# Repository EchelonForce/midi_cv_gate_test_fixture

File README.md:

# MIDI to 16x16 CV Gate Module Test Fixture

This the KiCAD design of a test fixture for the MIDI to 16x16 CV Gate Module

Full writeup here: https://www.robotdialogs.com/2023/03/test-fixture-and-calibration-eurorack.html

This work is licensed under a Creative Commons Attribution-NonCommercial-ShareAlike 4.0 International License. https://creativecommons.org/licenses/by-nc-sa/4.0/

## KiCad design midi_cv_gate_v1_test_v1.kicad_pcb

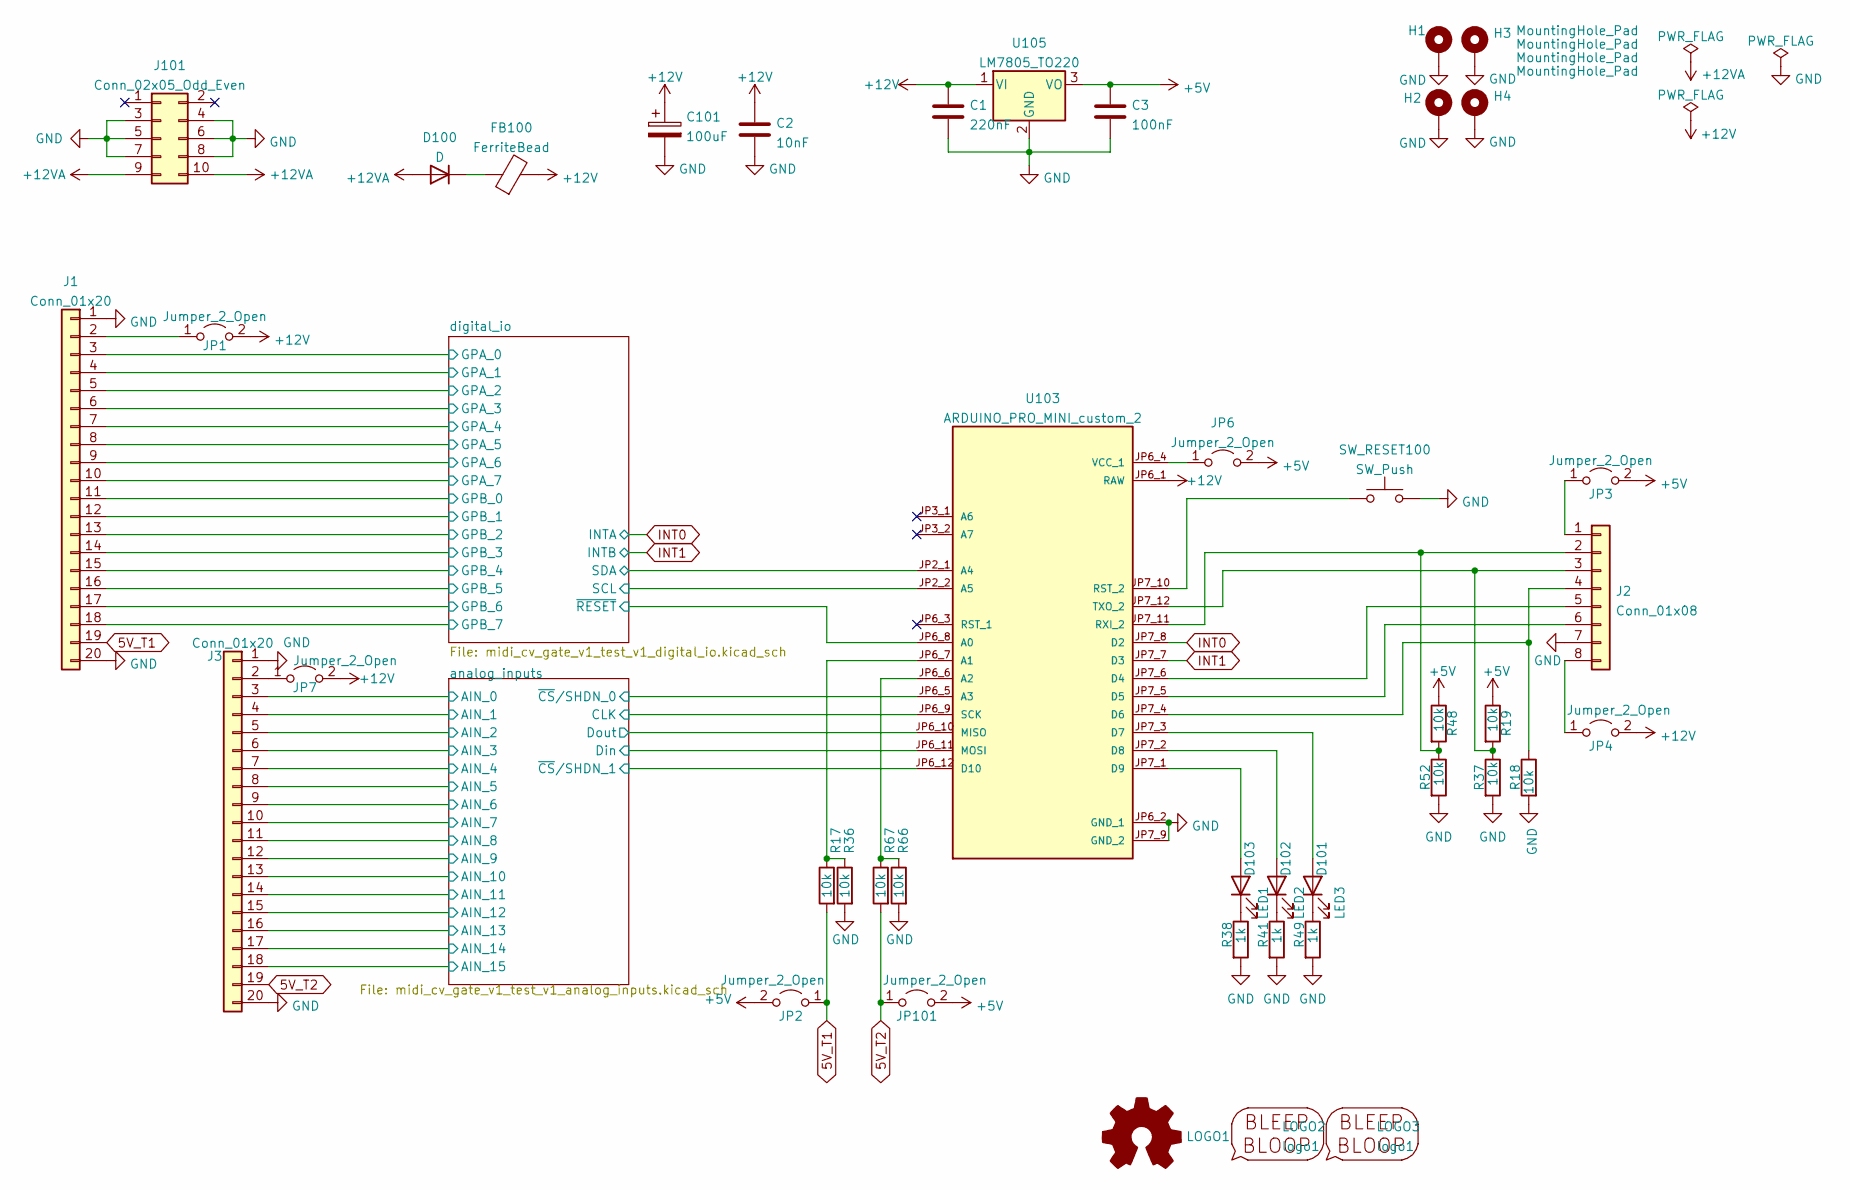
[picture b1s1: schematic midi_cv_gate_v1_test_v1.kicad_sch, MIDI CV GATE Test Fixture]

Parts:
C1: 220nF; C_1206_3216Metric_Pad1.33x1.80mm_HandSolder
C2: 10nF; C_1206_3216Metric_Pad1.33x1.80mm_HandSolder
C3: 100nF; C_1206_3216Metric_Pad1.33x1.80mm_HandSolder
C101: 100uF; CP_Radial_D5.0mm_P2.50mm
D100: D; D_A-405_P2.54mm_Vertical_KathodeUp
D101: LED3; LED_D3.0mm
D102: LED2; LED_D3.0mm
D103: LED1; LED_D3.0mm
FB100: FerriteBead; L_Axial_L6.6mm_D2.7mm_P2.54mm_Vertical_Vishay_IM-2
H1, H2, H3, H4: MountingHole_Pad; MountingHole_3.2mm_M3_ISO7380_Pad_TopBottom
J1, J3: Conn_01x20; PinSocket_1x20_P2.54mm_Vertical
J2: Conn_01x08; PinSocket_1x08_P2.54mm_Vertical
J101: Conn_02x05_Odd_Even; IDC-Header_2x05_P2.54mm_Vertical
JP1, JP2, JP3, JP4, JP6, JP7, JP101: Jumper_2_Open; SolderJumper-2_P1.3mm_Open_Pad1.0x1.5mm
LOGO1: Logo_Open_Hardware_Small; OSHW-Symbol_6.7x6mm_SilkScreen
LOGO2: logo1; Logo1
LOGO3: logo1; Logo2
R17, R18, R19, R36, R37, R48, R52, R66, R67: 10k; R_1206_3216Metric_Pad1.30x1.75mm_HandSolder
R38, R41, R49: 1k; R_1206_3216Metric_Pad1.30x1.75mm_HandSolder
SW_RESET100: SW_Push; SW_PUSH_6mm_H5mm
U103: ARDUINO_PRO_MINI_custom_2; MODULE_ARDUINO_PRO_MINI_custom_2; PARTREV N/A
U105: LM7805_TO220; TO-220-3_Horizontal_TabDown

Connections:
5V_T1: J1.19, JP2.1 (A), R17.2
5V_T2: J3.19, JP101.1 (A), R67.2
+5V: C3.1, JP2.2 (B), JP3.2 (B), JP6.2 (B), JP101.2 (B), R19.1, R48.1, U105.3 (VO); also elsewhere on the board
+12V: C1.1, C2.1, C101.1, FB100.2, JP1.2 (B), JP4.2 (B), JP7.2 (B), U103.JP6_1 (RAW), U105.1 (VI); also elsewhere on the board
+12VA: D100.2 (A), J101.9, J101.10
/analog_inputs/AIN_0: J3.3; also elsewhere on the board
/analog_inputs/AIN_1: J3.4; also elsewhere on the board
/analog_inputs/AIN_2: J3.5; also elsewhere on the board
/analog_inputs/AIN_3: J3.6; also elsewhere on the board
/analog_inputs/AIN_4: J3.7; also elsewhere on the board
/analog_inputs/AIN_5: J3.8; also elsewhere on the board
/analog_inputs/AIN_6: J3.9; also elsewhere on the board
/analog_inputs/AIN_7: J3.10; also elsewhere on the board
/analog_inputs/AIN_8: J3.11; also elsewhere on the board
/analog_inputs/AIN_9: J3.12; also elsewhere on the board
/analog_inputs/AIN_10: J3.13; also elsewhere on the board
/analog_inputs/AIN_11: J3.14; also elsewhere on the board
/analog_inputs/AIN_12: J3.15; also elsewhere on the board
/analog_inputs/AIN_13: J3.16; also elsewhere on the board
/analog_inputs/AIN_14: J3.17; also elsewhere on the board
/analog_inputs/AIN_15: J3.18; also elsewhere on the board
/analog_inputs/CLK: U103.JP6_9 (SCK); also elsewhere on the board
/analog_inputs/Din: U103.JP6_11 (MOSI); also elsewhere on the board
/analog_inputs/Dout: U103.JP6_10 (MISO); also elsewhere on the board
/analog_inputs/~CS/SHDN_0: U103.JP6_5 (A3); also elsewhere on the board
/analog_inputs/~CS/SHDN_1: U103.JP6_12 (D10); also elsewhere on the board
/digital_io/GPA_0: J1.3; also elsewhere on the board
/digital_io/GPA_1: J1.4; also elsewhere on the board
/digital_io/GPA_2: J1.5; also elsewhere on the board
/digital_io/GPA_3: J1.6; also elsewhere on the board
/digital_io/GPA_4: J1.7; also elsewhere on the board
/digital_io/GPA_5: J1.8; also elsewhere on the board
/digital_io/GPA_6: J1.9; also elsewhere on the board
/digital_io/GPA_7: J1.10; also elsewhere on the board
/digital_io/GPB_0: J1.11; also elsewhere on the board
/digital_io/GPB_1: J1.12; also elsewhere on the board
/digital_io/GPB_2: J1.13; also elsewhere on the board
/digital_io/GPB_3: J1.14; also elsewhere on the board
/digital_io/GPB_4: J1.15; also elsewhere on the board
/digital_io/GPB_5: J1.16; also elsewhere on the board
/digital_io/GPB_6: J1.17; also elsewhere on the board
/digital_io/GPB_7: J1.18; also elsewhere on the board
/digital_io/SCL: U103.JP2_2 (A5); also elsewhere on the board
/digital_io/SDA: U103.JP2_1 (A4); also elsewhere on the board
/digital_io/~RESET: U103.JP6_8 (A0); also elsewhere on the board
GND: C1.2, C2.2, C3.2, C101.2, H1.1, H2.1, H3.1, H4.1, J1.1, J1.20, J2.7, J3.1, J3.20, J101.3, J101.4, J101.5, J101.6, J101.7, J101.8, R18.2, R36.2, R37.2, R38.2, R41.2, R49.2, R52.2, R66.2, SW_RESET100.2, U103.JP6_2 (GND_1), U103.JP7_9 (GND_2), U105.2 (GND); also elsewhere on the board
INT0: U103.JP7_8 (D2); also elsewhere on the board
INT1: U103.JP7_7 (D3); also elsewhere on the board
unnamed: D100.1 (K), FB100.1
unnamed: D101.1 (K), R49.1
unnamed: D101.2 (A), U103.JP7_3 (D7)
unnamed: D102.1 (K), R41.1
unnamed: D102.2 (A), U103.JP7_2 (D8)
unnamed: D103.1 (K), R38.1
unnamed: D103.2 (A), U103.JP7_1 (D9)
unnamed: J1.2, JP1.1 (A)
unnamed: J2.1, JP3.1 (A)
unnamed: J2.2, R48.2, R52.1, U103.JP7_11 (RXI_2)
unnamed: J2.3, R18.1, R19.2, U103.JP7_12 (TXO_2)
unnamed: J2.4, R37.1, U103.JP7_4 (D6)
unnamed: J2.5, U103.JP7_6 (D4)
unnamed: J2.6, U103.JP7_5 (D5)
unnamed: J2.8, JP4.1 (A)
unnamed: J3.2, JP7.1 (A)
unnamed: JP6.1 (A), U103.JP6_4 (VCC_1)
unnamed: R17.1, R36.1, U103.JP6_7 (A1)
unnamed: R66.1, R67.1, U103.JP6_6 (A2)
unnamed: SW_RESET100.1, U103.JP7_10 (RST_2)

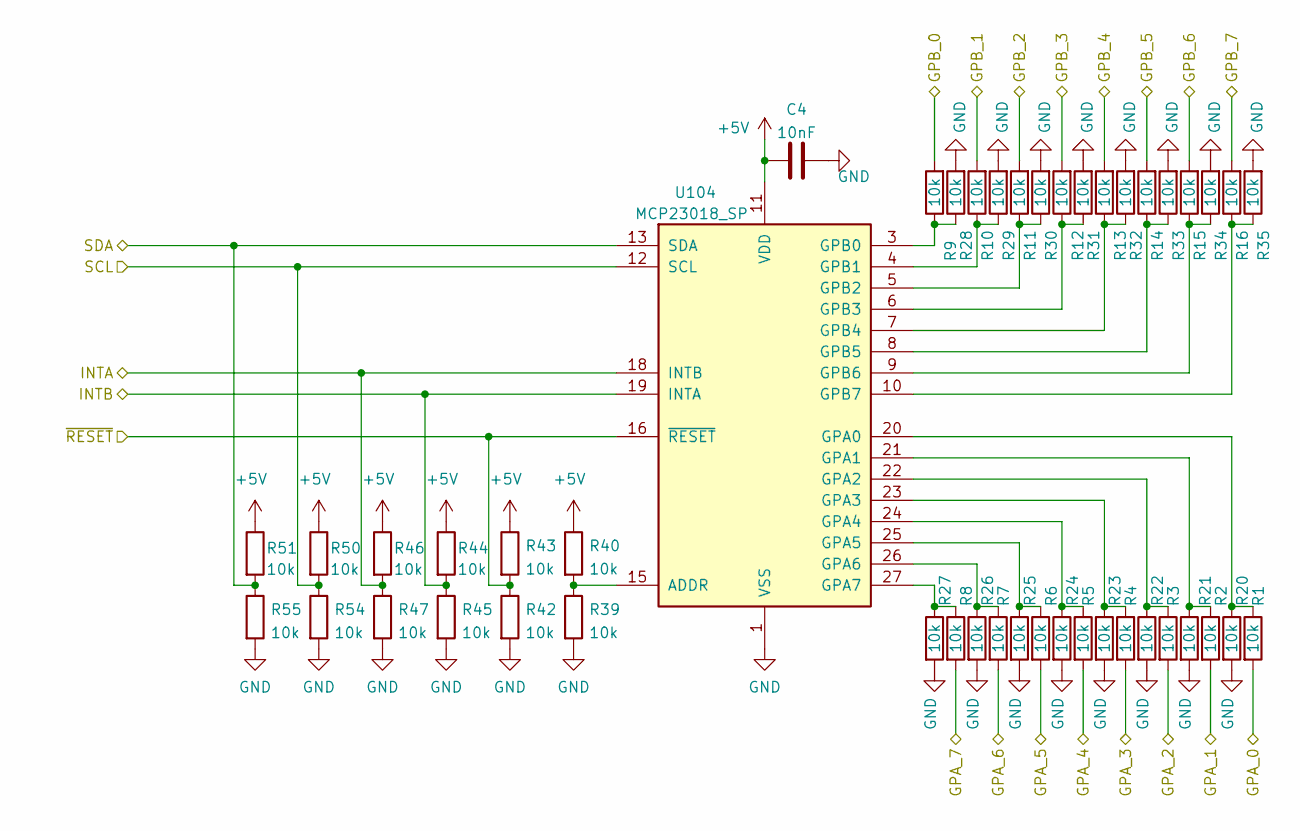
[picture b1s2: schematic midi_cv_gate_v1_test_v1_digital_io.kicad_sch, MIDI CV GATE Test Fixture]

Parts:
C4: 10nF; C_1206_3216Metric_Pad1.33x1.80mm_HandSolder
R1, R2, R3, R4, R5, R6, R7, R8, R9, R10, R11, R12, R13, R14, R15, R16, R20, R21, R22, R23, R24, R25, R26, R27, R28, R29, R30, R31, R32, R33, R34, R35, R39, R40, R42, R43, R44, R45, R46, R47, R50, R51, R54, R55: 10k; R_1206_3216Metric_Pad1.30x1.75mm_HandSolder
U104: MCP23018_SP; DIP-28_W7.62mm_Socket_LongPads

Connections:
+5V: C4.2, R40.1, R43.1, R44.1, R46.1, R50.1, R51.1, U104.11 (VDD); also elsewhere on the board
/digital_io/GPA_0: R1.2; also elsewhere on the board
/digital_io/GPA_1: R2.2; also elsewhere on the board
/digital_io/GPA_2: R3.2; also elsewhere on the board
/digital_io/GPA_3: R4.2; also elsewhere on the board
/digital_io/GPA_4: R5.2; also elsewhere on the board
/digital_io/GPA_5: R6.2; also elsewhere on the board
/digital_io/GPA_6: R7.2; also elsewhere on the board
/digital_io/GPA_7: R8.2; also elsewhere on the board
/digital_io/GPB_0: R9.2; also elsewhere on the board
/digital_io/GPB_1: R10.2; also elsewhere on the board
/digital_io/GPB_2: R11.2; also elsewhere on the board
/digital_io/GPB_3: R12.2; also elsewhere on the board
/digital_io/GPB_4: R13.2; also elsewhere on the board
/digital_io/GPB_5: R14.2; also elsewhere on the board
/digital_io/GPB_6: R15.2; also elsewhere on the board
/digital_io/GPB_7: R16.2; also elsewhere on the board
/digital_io/SCL: R50.2, R54.1, U104.12 (SCL); also elsewhere on the board
/digital_io/SDA: R51.2, R55.1, U104.13 (SDA); also elsewhere on the board
/digital_io/~RESET: R42.1, R43.2, U104.16 (~RESET); also elsewhere on the board
GND: C4.1, R20.2, R21.2, R22.2, R23.2, R24.2, R25.2, R26.2, R27.2, R28.2, R29.2, R30.2, R31.2, R32.2, R33.2, R34.2, R35.2, R39.2, R42.2, R45.2, R47.2, R54.2, R55.2, U104.1 (VSS); also elsewhere on the board
INT0: R46.2, R47.1, U104.18 (INTB); also elsewhere on the board
INT1: R44.2, R45.1, U104.19 (INTA); also elsewhere on the board
unnamed: R1.1, R20.1, U104.20 (GPA0)
unnamed: R2.1, R21.1, U104.21 (GPA1)
unnamed: R10.1, R29.1, U104.4 (GPB1)
unnamed: R11.1, R30.1, U104.5 (GPB2)
unnamed: R12.1, R31.1, U104.6 (GPB3)
unnamed: R13.1, R32.1, U104.7 (GPB4)
unnamed: R14.1, R33.1, U104.8 (GPB5)
unnamed: R15.1, R34.1, U104.9 (GPB6)
unnamed: R16.1, R35.1, U104.10 (GPB7)
unnamed: R3.1, R22.1, U104.22 (GPA2)
unnamed: R4.1, R23.1, U104.23 (GPA3)
unnamed: R5.1, R24.1, U104.24 (GPA4)
unnamed: R6.1, R25.1, U104.25 (GPA5)
unnamed: R7.1, R26.1, U104.26 (GPA6)
unnamed: R8.1, R27.1, U104.27 (GPA7)
unnamed: R9.1, R28.1, U104.3 (GPB0)
unnamed: R39.1, R40.2, U104.15 (ADDR)

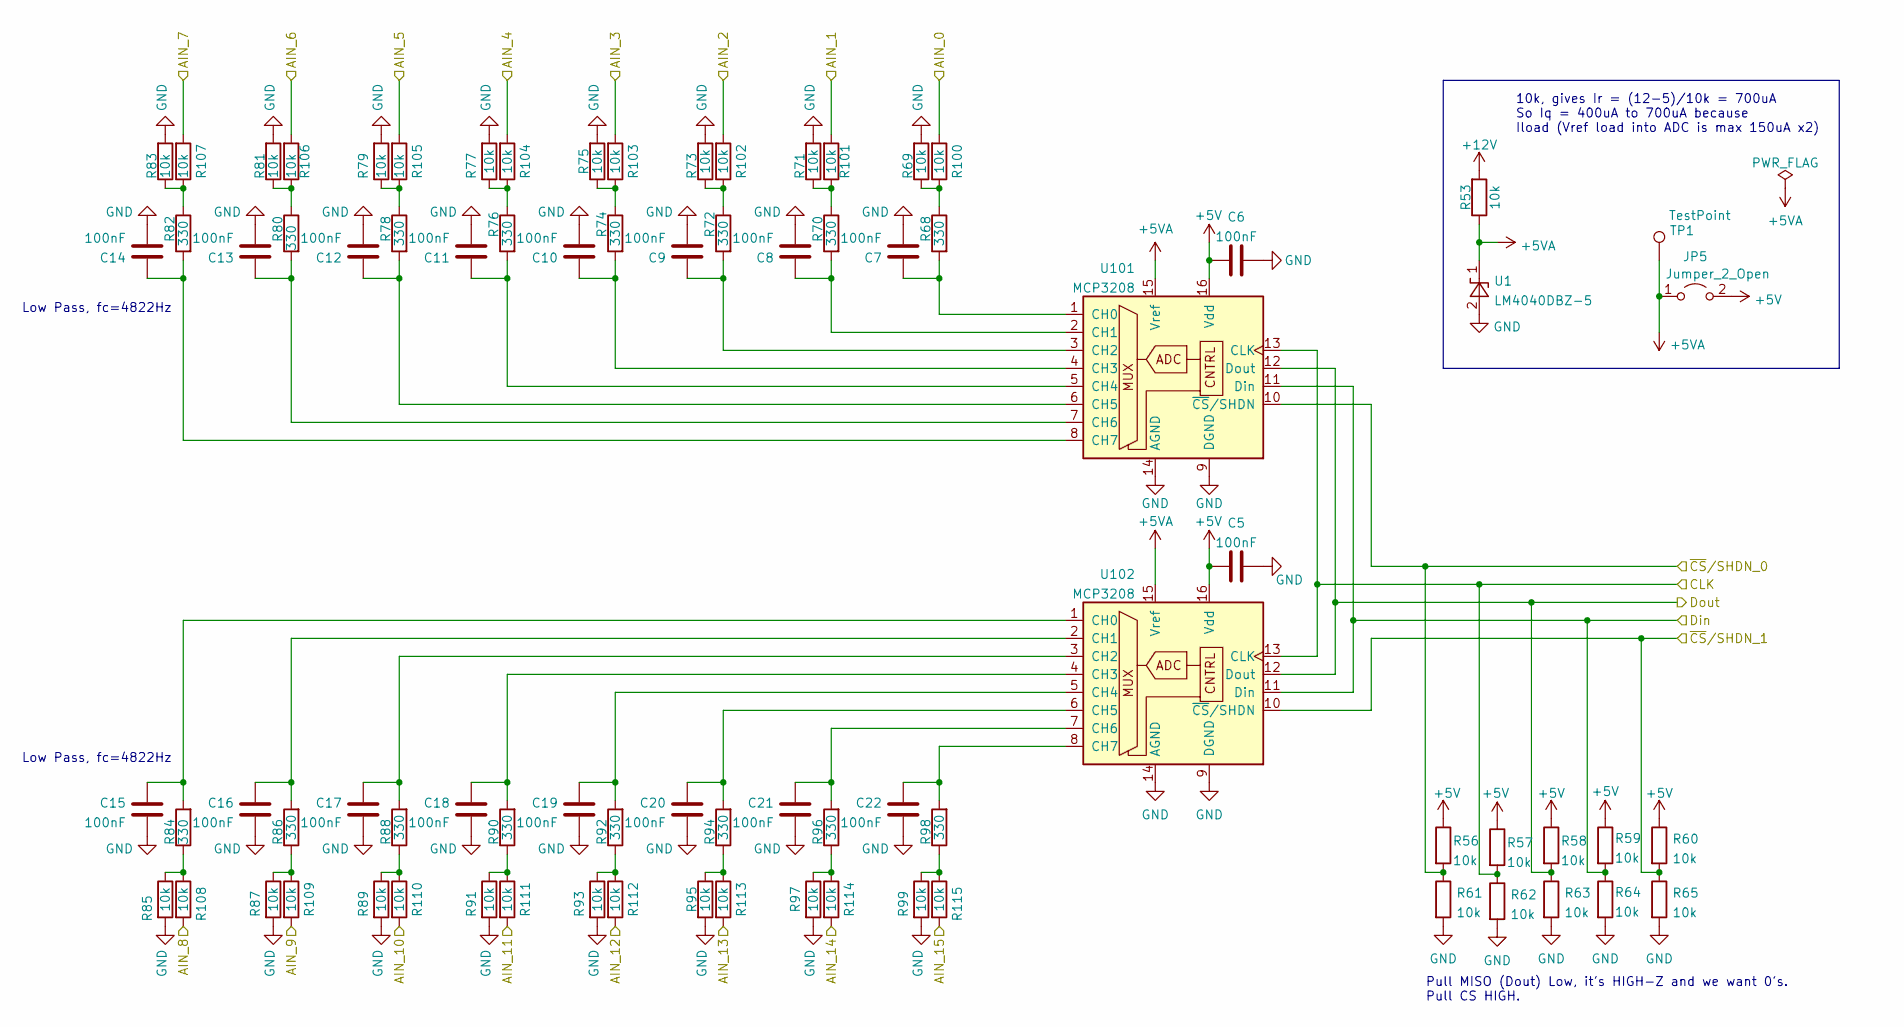
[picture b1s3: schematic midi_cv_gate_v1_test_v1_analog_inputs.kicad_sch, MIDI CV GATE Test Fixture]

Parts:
C5, C6, C7, C8, C9, C10, C11, C12, C13, C14, C15, C16, C17, C18, C19, C20, C21, C22: 100nF; C_1206_3216Metric_Pad1.33x1.80mm_HandSolder
JP5: Jumper_2_Open; SolderJumper-2_P1.3mm_Open_Pad1.0x1.5mm
R53, R56, R57, R58, R59, R60, R61, R62, R63, R64, R65, R69, R71, R73, R75, R77, R79, R81, R83, R85, R87, R89, R91, R93, R95, R97, R99, R100, R101, R102, R103, R104, R105, R106, R107, R108, R109, R110, R111, R112, R113, R114, R115: 10k; R_1206_3216Metric_Pad1.30x1.75mm_HandSolder
R68, R70, R72, R74, R76, R78, R80, R82, R84, R86, R88, R90, R92, R94, R96, R98: 330; R_1206_3216Metric_Pad1.30x1.75mm_HandSolder
TP1: TestPoint; TestPoint_THTPad_2.0x2.0mm_Drill1.0mm
U1: LM4040DBZ-5; SOT-23
U101, U102: MCP3208; DIP-16_W7.62mm_Socket_LongPads

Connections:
+5V: C5.2, C6.2, JP5.2 (B), R56.1, R57.1, R58.1, R59.1, R60.1, U101.16 (Vdd), U102.16 (Vdd); also elsewhere on the board
+5VA: JP5.1 (A), R53.1, TP1.1, U1.1 (K), U101.15 (Vref), U102.15 (Vref)
+12V: R53.2; also elsewhere on the board
/analog_inputs/AIN_0: R100.2; also elsewhere on the board
/analog_inputs/AIN_1: R101.2; also elsewhere on the board
/analog_inputs/AIN_2: R102.2; also elsewhere on the board
/analog_inputs/AIN_3: R103.2; also elsewhere on the board
/analog_inputs/AIN_4: R104.2; also elsewhere on the board
/analog_inputs/AIN_5: R105.2; also elsewhere on the board
/analog_inputs/AIN_6: R106.2; also elsewhere on the board
/analog_inputs/AIN_7: R107.2; also elsewhere on the board
/analog_inputs/AIN_8: R108.2; also elsewhere on the board
/analog_inputs/AIN_9: R109.2; also elsewhere on the board
/analog_inputs/AIN_10: R110.2; also elsewhere on the board
/analog_inputs/AIN_11: R111.2; also elsewhere on the board
/analog_inputs/AIN_12: R112.2; also elsewhere on the board
/analog_inputs/AIN_13: R113.2; also elsewhere on the board
/analog_inputs/AIN_14: R114.2; also elsewhere on the board
/analog_inputs/AIN_15: R115.2; also elsewhere on the board
/analog_inputs/CLK: R57.2, R62.1, U101.13 (CLK), U102.13 (CLK); also elsewhere on the board
/analog_inputs/Din: R59.2, R64.1, U101.11 (Din), U102.11 (Din); also elsewhere on the board
/analog_inputs/Dout: R58.2, R63.1, U101.12 (Dout), U102.12 (Dout); also elsewhere on the board
/analog_inputs/~CS/SHDN_0: R56.2, R61.1, U101.10 (~CS/SHDN); also elsewhere on the board
/analog_inputs/~CS/SHDN_1: R60.2, R65.1, U102.10 (~CS/SHDN); also elsewhere on the board
GND: C5.1, C6.1, C7.2, C8.2, C9.2, C10.2, C11.2, C12.2, C13.2, C14.2, C15.2, C16.2, C17.2, C18.2, C19.2, C20.2, C21.2, C22.2, R61.2, R62.2, R63.2, R64.2, R65.2, R69.2, R71.2, R73.2, R75.2, R77.2, R79.2, R81.2, R83.2, R85.2, R87.2, R89.2, R91.2, R93.2, R95.2, R97.2, R99.2, U1.2 (A), U101.9 (DGND), U101.14 (AGND), U102.9 (DGND), U102.14 (AGND); also elsewhere on the board
unnamed: C7.1, R68.2, U101.1 (CH0)
unnamed: C8.1, R70.2, U101.2 (CH1)
unnamed: C9.1, R72.2, U101.3 (CH2)
unnamed: C10.1, R74.2, U101.4 (CH3)
unnamed: C11.1, R76.2, U101.5 (CH4)
unnamed: C12.1, R78.2, U101.6 (CH5)
unnamed: C13.1, R80.2, U101.7 (CH6)
unnamed: C14.1, R82.2, U101.8 (CH7)
unnamed: C15.1, R84.2, U102.1 (CH0)
unnamed: C16.1, R86.2, U102.2 (CH1)
unnamed: C17.1, R88.2, U102.3 (CH2)
unnamed: C18.1, R90.2, U102.4 (CH3)
unnamed: C19.1, R92.2, U102.5 (CH4)
unnamed: C20.1, R94.2, U102.6 (CH5)
unnamed: C21.1, R96.2, U102.7 (CH6)
unnamed: C22.1, R98.2, U102.8 (CH7)
unnamed: R68.1, R69.1, R100.1
unnamed: R70.1, R71.1, R101.1
unnamed: R72.1, R73.1, R102.1
unnamed: R74.1, R75.1, R103.1
unnamed: R76.1, R77.1, R104.1
unnamed: R78.1, R79.1, R105.1
unnamed: R80.1, R81.1, R106.1
unnamed: R82.1, R83.1, R107.1
unnamed: R84.1, R85.1, R108.1
unnamed: R86.1, R87.1, R109.1
unnamed: R88.1, R89.1, R110.1
unnamed: R90.1, R91.1, R111.1
unnamed: R92.1, R93.1, R112.1
unnamed: R94.1, R95.1, R113.1
unnamed: R96.1, R97.1, R114.1
unnamed: R98.1, R99.1, R115.1

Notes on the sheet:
10k, gives Ir = (12-5)/10k = 700uA So Iq = 400uA to 700uA because Iload (Vref load into ADC is max 150uA x2)
Pull MISO (Dout) Low, it's HIGH-Z and we want 0's. Pull CS HIGH.
Low Pass, fc=4822Hz

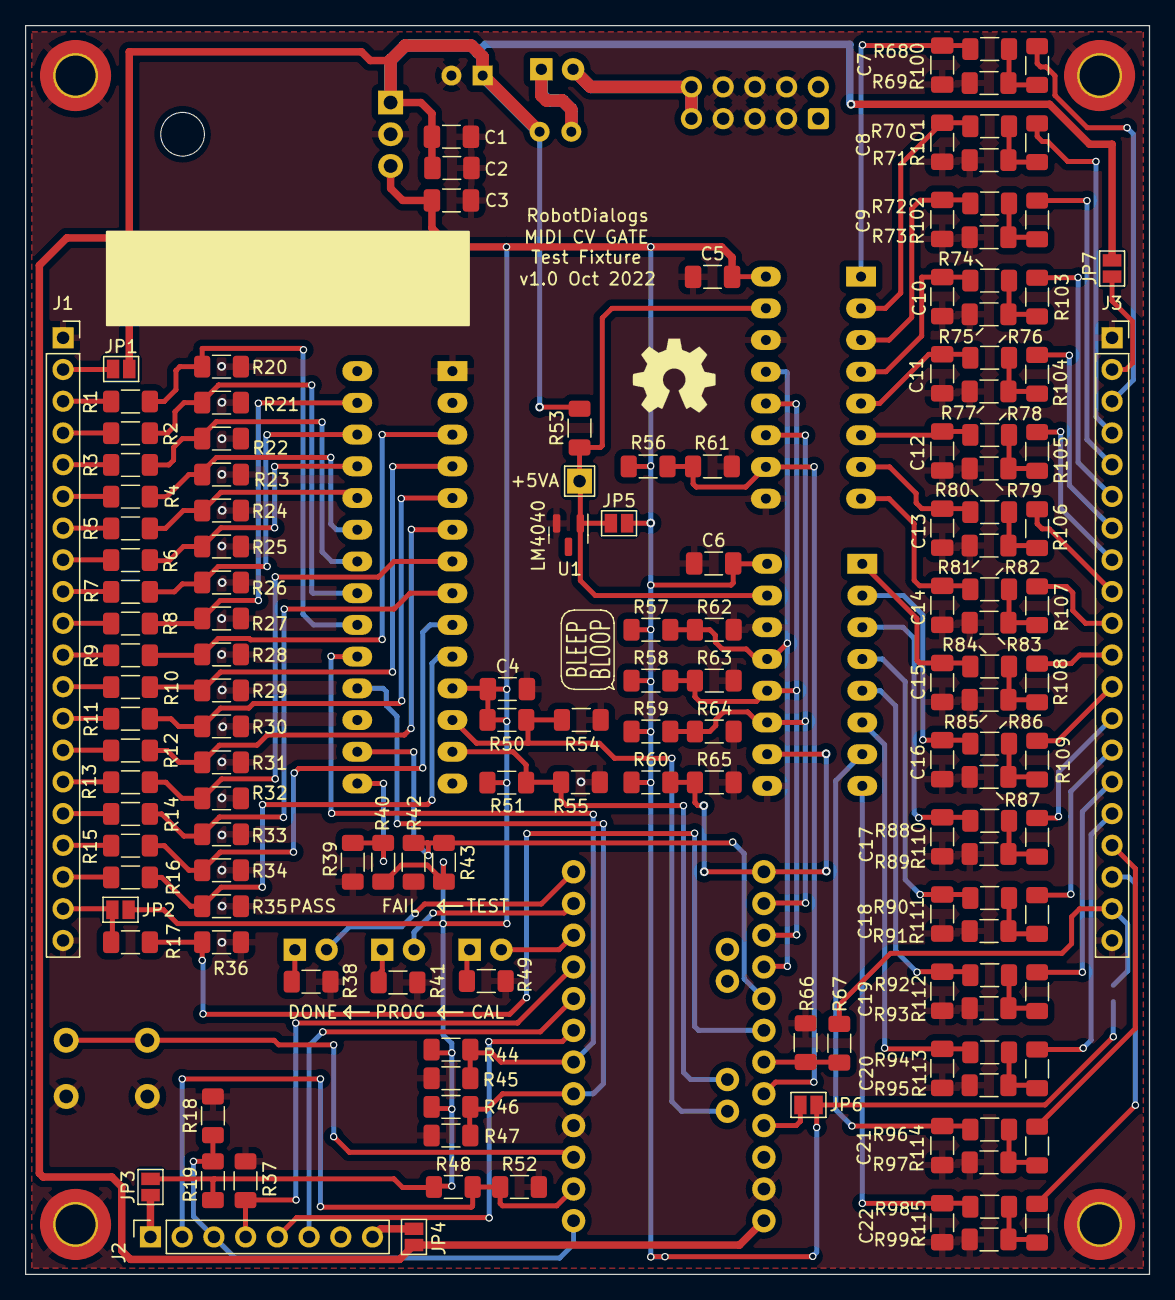
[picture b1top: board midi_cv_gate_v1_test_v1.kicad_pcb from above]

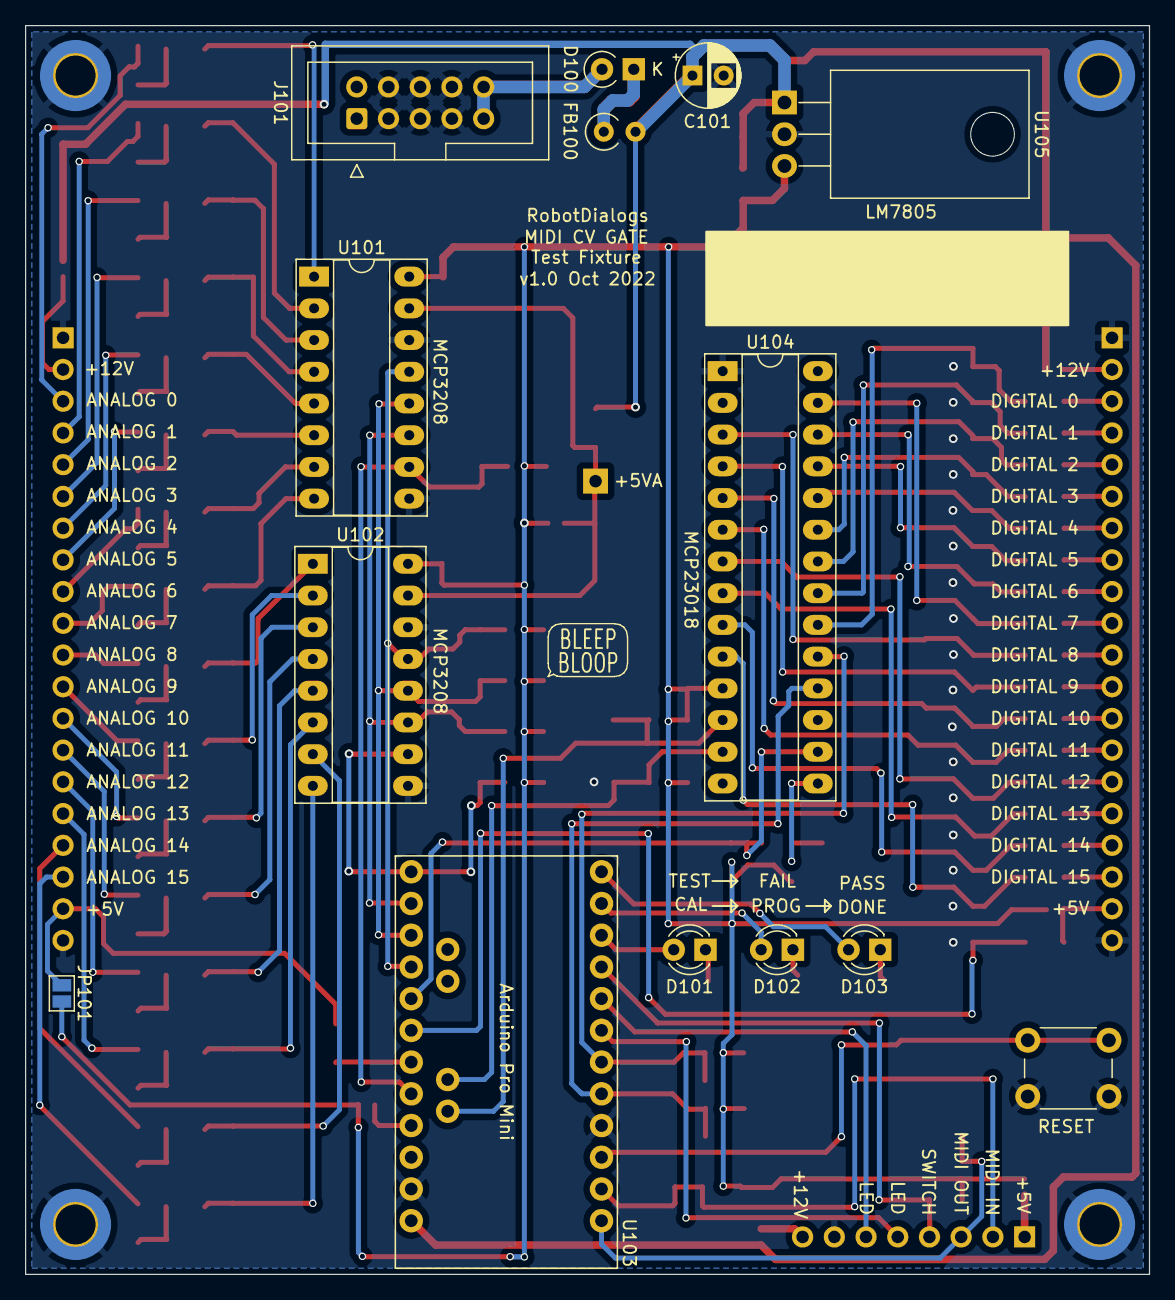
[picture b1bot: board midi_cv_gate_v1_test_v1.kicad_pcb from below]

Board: 2 copper layers, 90.0 x 100.0 mm, 170 parts (14 on the bottom side), 118 nets.

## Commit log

2022-10-01 Initial commit with .gitignore
2022-10-01 Add readme
2022-10-01 Schematic mostly figured out
2022-10-02 Component positions first draft
2022-10-02 First pass routing done
2022-10-02 Geographic re-annotate
2022-10-02 Silkscreen cleanup and title block filled
2022-10-10 A little cleanup
2022-10-10 Output script for v1
2022-10-15 Resync pcb and schematic
2022-10-15 Add schematic pdf
2023-03-04 Component updates and rework info v1
2023-03-04 Fix link in README
